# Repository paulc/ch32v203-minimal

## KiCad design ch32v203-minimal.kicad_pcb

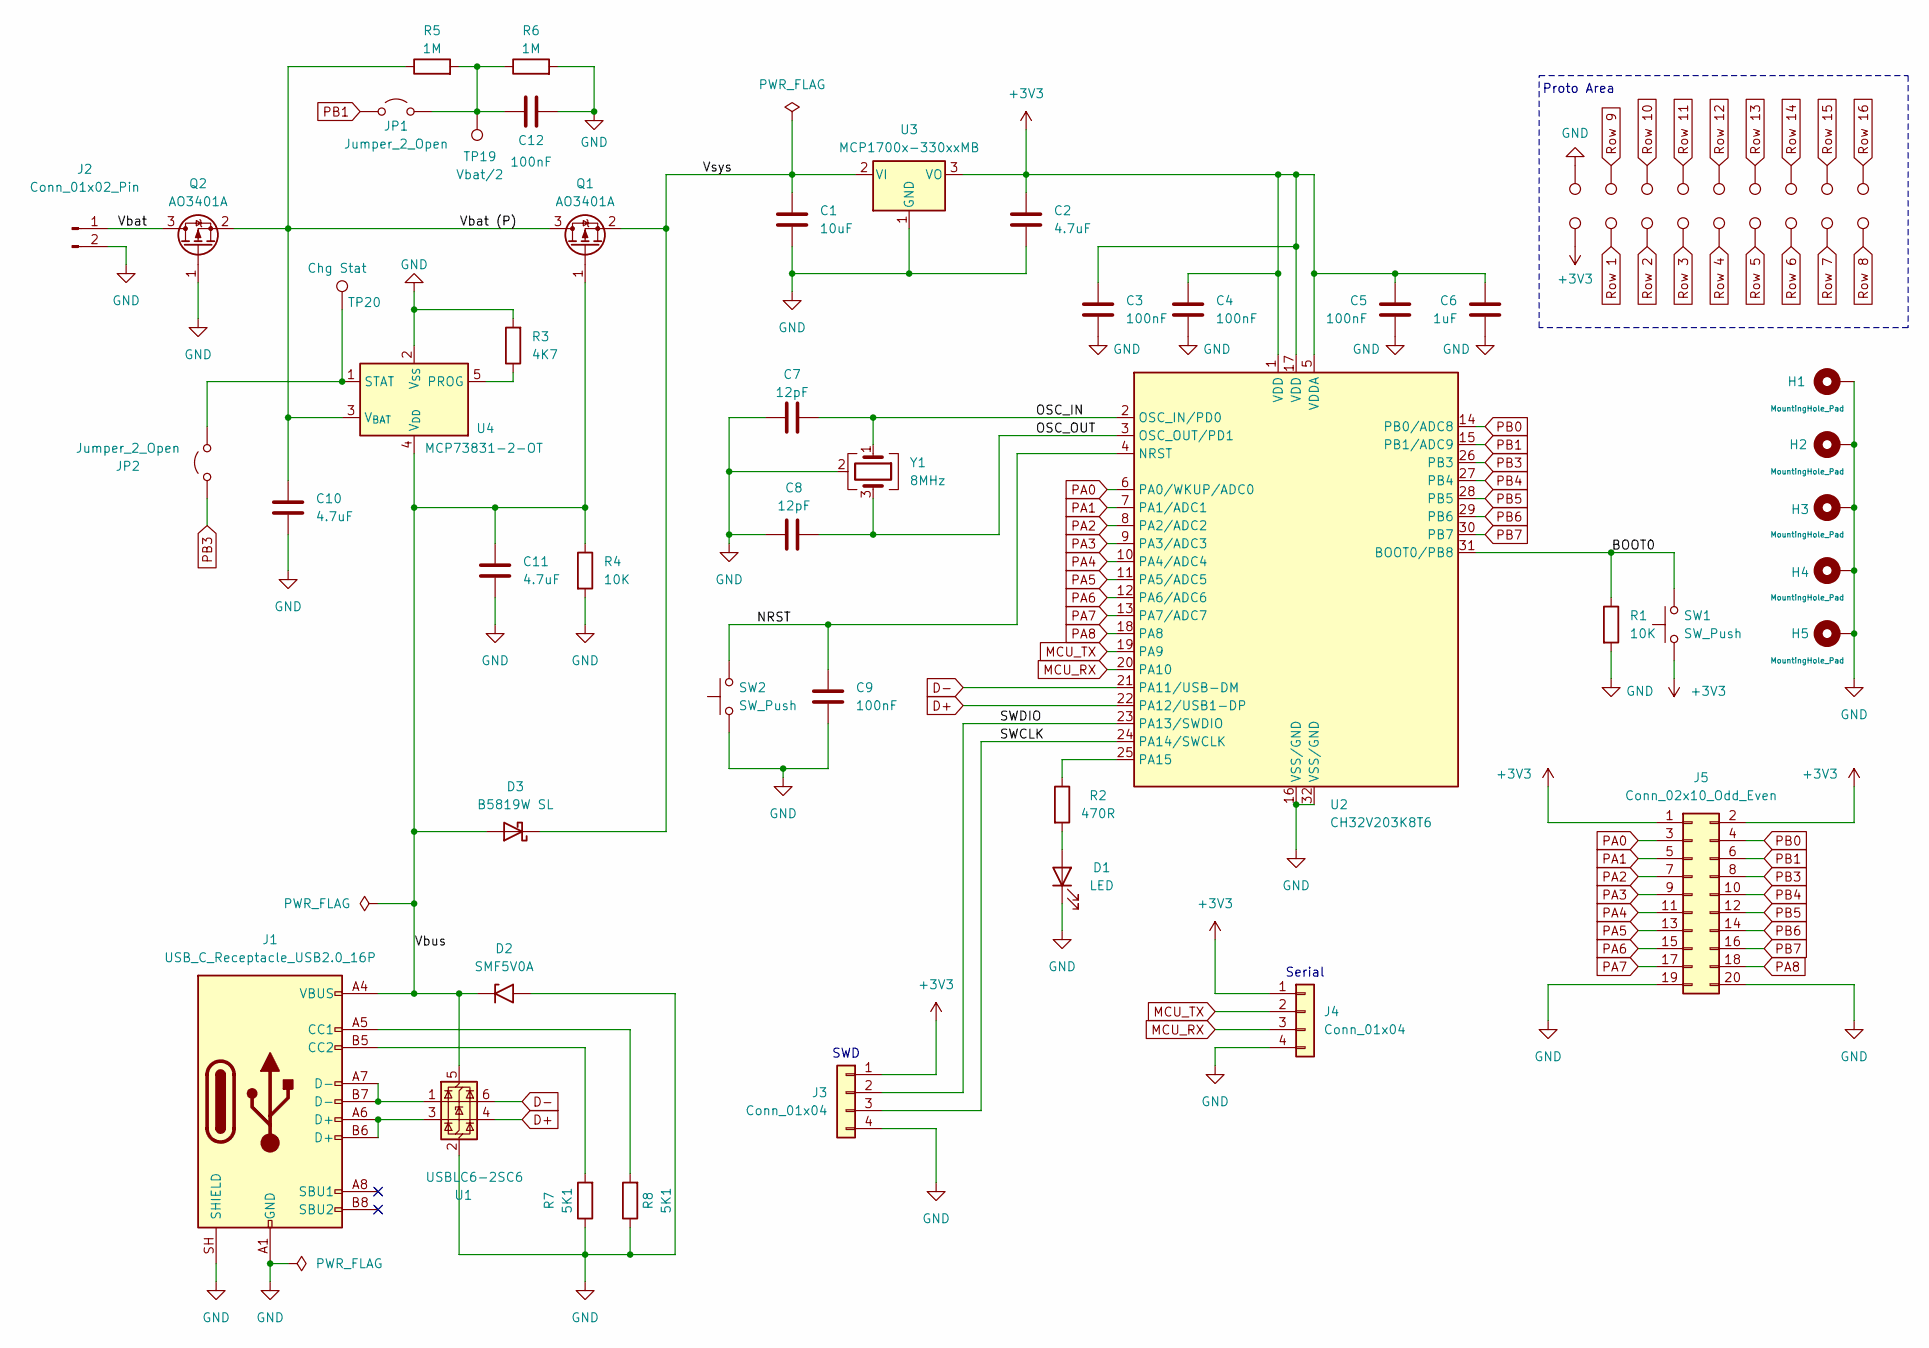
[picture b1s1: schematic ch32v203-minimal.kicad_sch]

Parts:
C1: 10uF; C_1206_3216Metric_Pad1.33x1.80mm_HandSolder; LCSC C13585
C2, C10, C11: 4.7uF; C_1206_3216Metric_Pad1.33x1.80mm_HandSolder; LCSC C29823
C3, C4, C5, C9, C12: 100nF; C_1206_3216Metric_Pad1.33x1.80mm_HandSolder; LCSC C24497
C6: 1uF; C_1206_3216Metric_Pad1.33x1.80mm_HandSolder; LCSC C1848
C7, C8: 12pF; C_1206_3216Metric_Pad1.33x1.80mm_HandSolder; LCSC C47118551
D1: LED; LED_1206_3216Metric_Pad1.42x1.75mm_HandSolder; LCSC C2827254
D2: SMF5V0A; D_SMF; LCSC C1972946
D3: B5819W SL; D_SOD-123; LCSC C8598
H1, H2, H3, H4, H5: MountingHole_Pad; MountingHole_2.2mm_M2_DIN965_Pad
J1: USB_C_Receptacle_USB2.0_16P; USB_C_Receptacle_HRO_TYPE-C-31-M-12; LCSC C165948
J2: Conn_01x02_Pin; JST_PH_B2B-PH-K_1x02_P2.00mm_Vertical; LCSC C131337
J3, J4: Conn_01x04; PinHeader_1x04_P2.54mm_Vertical
J5: Conn_02x10_Odd_Even; PinHeader_2x10_P2.54mm_Vertical
JP1, JP2: Jumper_2_Open; SolderJumper-2_P1.3mm_Open_TrianglePad1.0x1.5mm
Q1, Q2: AO3401A; SOT-23; LCSC C15127
R1, R4: 10K; R_1206_3216Metric_Pad1.30x1.75mm_HandSolder; LCSC C17902
R2: 470R; R_1206_3216Metric_Pad1.30x1.75mm_HandSolder; LCSC C2930375
R3: 4K7; R_1206_3216Metric_Pad1.30x1.75mm_HandSolder; LCSC C17936
R5, R6: 1M; R_1206_3216Metric_Pad1.30x1.75mm_HandSolder; LCSC C17927
R7, R8: 5K1; R_1206_3216Metric_Pad1.30x1.75mm_HandSolder; LCSC C26033
SW1, SW2: SW_Push; 3_4_2 SMD Micro Touch Switch Button; LCSC Part C843659
TP1, TP2: TestPoint; Proto-1x16
TP3, TP4, TP5, TP6, TP7, TP8, TP9, TP10, TP11, TP12, TP13, TP14, TP15, TP16, TP17, TP18: TestPoint; Proto-1x4
TP19: Vbat/2; TestPoint_Pad_1.0x1.0mm
TP20: Chg Stat; TestPoint_Pad_1.0x1.0mm
U1: USBLC6-2SC6; SOT-23-6; LCSC C2687116
U2: CH32V203K8T6; LQFP-32_7x7mm_P0.8mm; LCSC C5372188
U3: MCP1700x-330xxMB; SOT-89-3; LCSC C632000
U4: MCP73831-2-OT; SOT-23-5; LCSC C424093
Y1: 8MHz; Crystal_SMD_3225-4Pin_3.2x2.5mm_HandSoldering; LCSC C400090

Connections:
+3V3: C2.1, C3.1, C4.1, C5.1, C6.1, J3.1, J4.1, J5.1, J5.2, SW1.1, TP2.1 (1_1), U2.1 (VDD), U2.5 (VDDA), U2.17 (VDD), U3.3 (VO)
/BOOT0: R1.1, SW1.2, U2.31 (BOOT0/PB8)
/NRST: C9.1, SW2.2, U2.4 (NRST)
/OSC_IN: C7.2, U2.2 (OSC_IN/PD0), Y1.1
/OSC_OUT: C8.2, U2.3 (OSC_OUT/PD1), Y1.3
/SWCLK: J3.3, U2.24 (PA14/SWCLK)
/SWDIO: J3.2, U2.23 (PA13/SWDIO)
/Vbat: J2.1, Q2.3 (D)
/Vbat (P): C10.1, Q1.3 (D), Q2.2 (S), R5.1, U4.3 (V_{BAT})
/Vbus: C11.1, D2.1 (A1), D3.2 (A), J1.A4 (VBUS), J1.A9 (VBUS), J1.B4 (VBUS), J1.B9 (VBUS), Q1.1 (G), R4.1, U1.5 (VBUS), U4.4 (V_{DD})
/Vsys: C1.1, D3.1 (K), Q1.2 (S), U3.2 (VI)
D+: U1.4 (I/O2), U2.22 (PA12/USB1-DP)
D-: U1.6 (I/O1), U2.21 (PA11/USB-DM)
GND: C1.2, C2.2, C3.2, C4.2, C5.2, C6.2, C7.1, C8.1, C9.2, C10.2, C11.2, C12.2, D1.1 (K), D2.2 (A2), H1.1 (1_1), H2.1 (1_1), H3.1 (1_1), H4.1 (1_1), H5.1 (1_1), J1.A1 (GND), J1.A12 (GND), J1.B1 (GND), J1.B12 (GND), J1.SH (SHIELD), J2.2, J3.4, J4.4, J5.19, J5.20, Q2.1 (G), R1.2, R3.2, R4.2, R6.2, R7.1, R8.1, SW2.1, TP1.1 (1_1), U1.2 (GND), U2.16 (VSS/GND), U2.32 (VSS/GND), U3.1 (GND), U4.2 (V_{SS}), Y1.2 (G), Y1.4 (G)
MCU_RX: J4.3, U2.20 (PA10)
MCU_TX: J4.2, U2.19 (PA9)
unnamed: D1.2 (A), R2.2
unnamed: J1.A5 (CC1), R8.2
unnamed: J1.B5 (CC2), R7.2
unnamed: J1.A6 (D+), J1.B6 (D+), U1.3 (I/O2)
unnamed: J1.A7 (D-), J1.B7 (D-), U1.1 (I/O1)
unnamed: C12.1, JP1.2 (B), R5.2, R6.1, TP19.1 (1_1)
unnamed: JP2.2 (B), TP20.1 (1_1), U4.1 (STAT)
unnamed: R2.1, U2.25 (PA15)
unnamed: R3.1, U4.5 (PROG)
PA0: J5.3, U2.6 (PA0/WKUP/ADC0)
PA1: J5.5, U2.7 (PA1/ADC1)
PA2: J5.7, U2.8 (PA2/ADC2)
PA3: J5.9, U2.9 (PA3/ADC3)
PA4: J5.11, U2.10 (PA4/ADC4)
PA5: J5.13, U2.11 (PA5/ADC5)
PA6: J5.15, U2.12 (PA6/ADC6)
PA7: J5.17, U2.13 (PA7/ADC7)
PA8: J5.18, U2.18 (PA8)
PB0: J5.4, U2.14 (PB0/ADC8)
PB1: J5.6, JP1.1 (A), U2.15 (PB1/ADC9)
PB3: J5.8, JP2.1 (A), U2.26 (PB3)
PB4: J5.10, U2.27 (PB4)
PB5: J5.12, U2.28 (PB5)
PB6: J5.14, U2.29 (PB6)
PB7: J5.16, U2.30 (PB7)
Row 1: TP3.1 (1_1)
Row 2: TP4.1 (1_1)
Row 3: TP5.1 (1_1)
Row 4: TP6.1 (1_1)
Row 5: TP7.1 (1_1)
Row 6: TP8.1 (1_1)
Row 7: TP9.1 (1_1)
Row 8: TP10.1 (1_1)
Row 9: TP11.1 (1_1)
Row 10: TP12.1 (1_1)
Row 11: TP13.1 (1_1)
Row 12: TP14.1 (1_1)
Row 13: TP15.1 (1_1)
Row 14: TP16.1 (1_1)
Row 15: TP17.1 (1_1)
Row 16: TP18.1 (1_1)

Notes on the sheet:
Serial
SWD
Proto Area

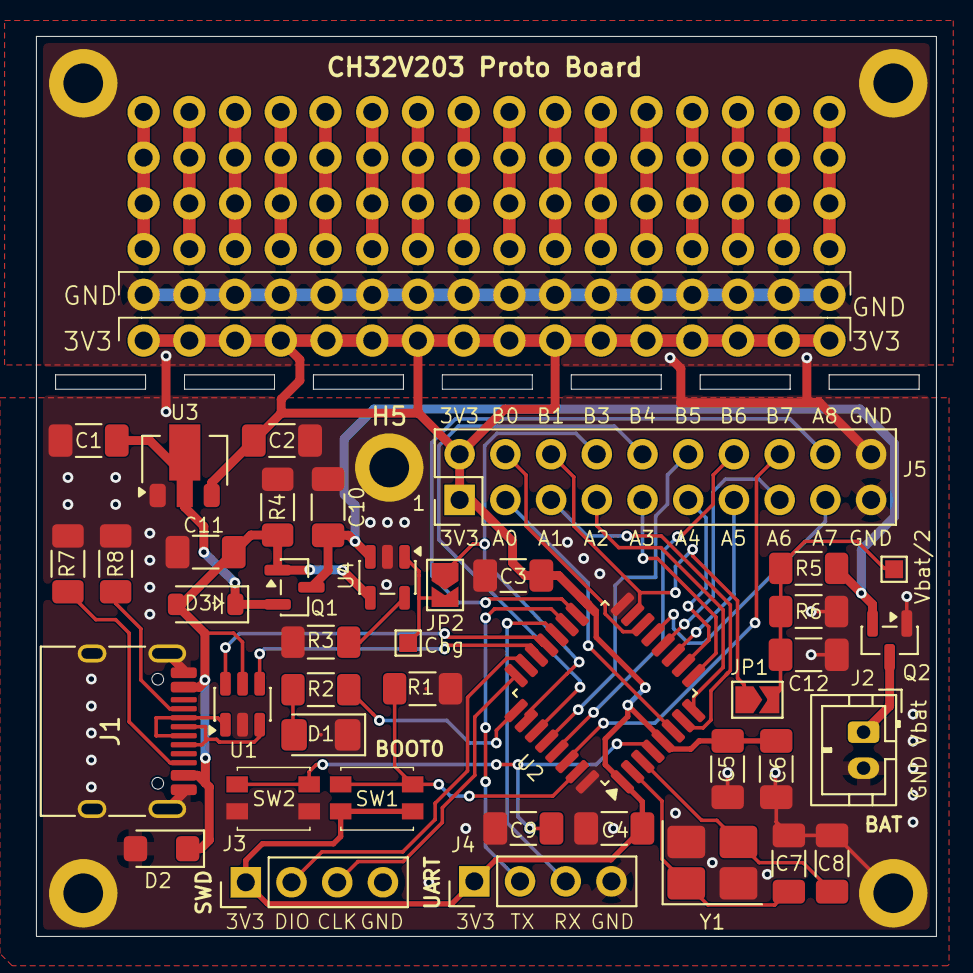
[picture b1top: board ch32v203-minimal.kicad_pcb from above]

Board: 2 copper layers, 50.0 x 50.0 mm, 64 parts (0 on the bottom side), 41 nets.

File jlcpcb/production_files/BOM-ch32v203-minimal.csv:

Comment,Designator,Footprint,LCSC,Quantity
100nF,"C12,C3,C4,C5,C9",C_1206_3216Metric_Pad1.33x1.80mm_HandSolder,C24497,5
10K,"R1,R4",R_1206_3216Metric_Pad1.30x1.75mm_HandSolder,C17902,2
10uF,C1,C_1206_3216Metric_Pad1.33x1.80mm_HandSolder,C13585,1
12pF,"C7,C8",C_1206_3216Metric_Pad1.33x1.80mm_HandSolder,C47118551,2
1M,"R5,R6",R_1206_3216Metric_Pad1.30x1.75mm_HandSolder,C17927,2
1uF,C6,C_1206_3216Metric_Pad1.33x1.80mm_HandSolder,C1848,1
4.7uF,"C10,C11,C2",C_1206_3216Metric_Pad1.33x1.80mm_HandSolder,C29823,3
470R,R2,R_1206_3216Metric_Pad1.30x1.75mm_HandSolder,C2930375,1
4K7,R3,R_1206_3216Metric_Pad1.30x1.75mm_HandSolder,C17936,1
5K1,"R7,R8",R_1206_3216Metric_Pad1.30x1.75mm_HandSolder,C26033,2
8MHz,Y1,Crystal_SMD_3225-4Pin_3.2x2.5mm_HandSoldering,C400090,1
AO3401A,"Q1,Q2",SOT-23,C15127,2
B5819W SL,D3,D_SOD-123,C8598,1
CH32V203K8T6,U2,LQFP-32_7x7mm_P0.8mm,C5372188,1
LED,D1,LED_1206_3216Metric_Pad1.42x1.75mm_HandSolder,C2827254,1
MCP1700x-330xxMB,U3,SOT-89-3,C632000,1
MCP73831-2-OT,U4,SOT-23-5,C424093,1
SMF5V0A,D2,D_SMF,C1972946,1
SW_Push,"SW1,SW2",3_4_2 SMD Micro Touch Switch Button,C843659,2
USBLC6-2SC6,U1,SOT-23-6,C2687116,1
USB_C_Receptacle_USB2.0_16P,J1,USB_C_Receptacle_HRO_TYPE-C-31-M-12,C165948,1
